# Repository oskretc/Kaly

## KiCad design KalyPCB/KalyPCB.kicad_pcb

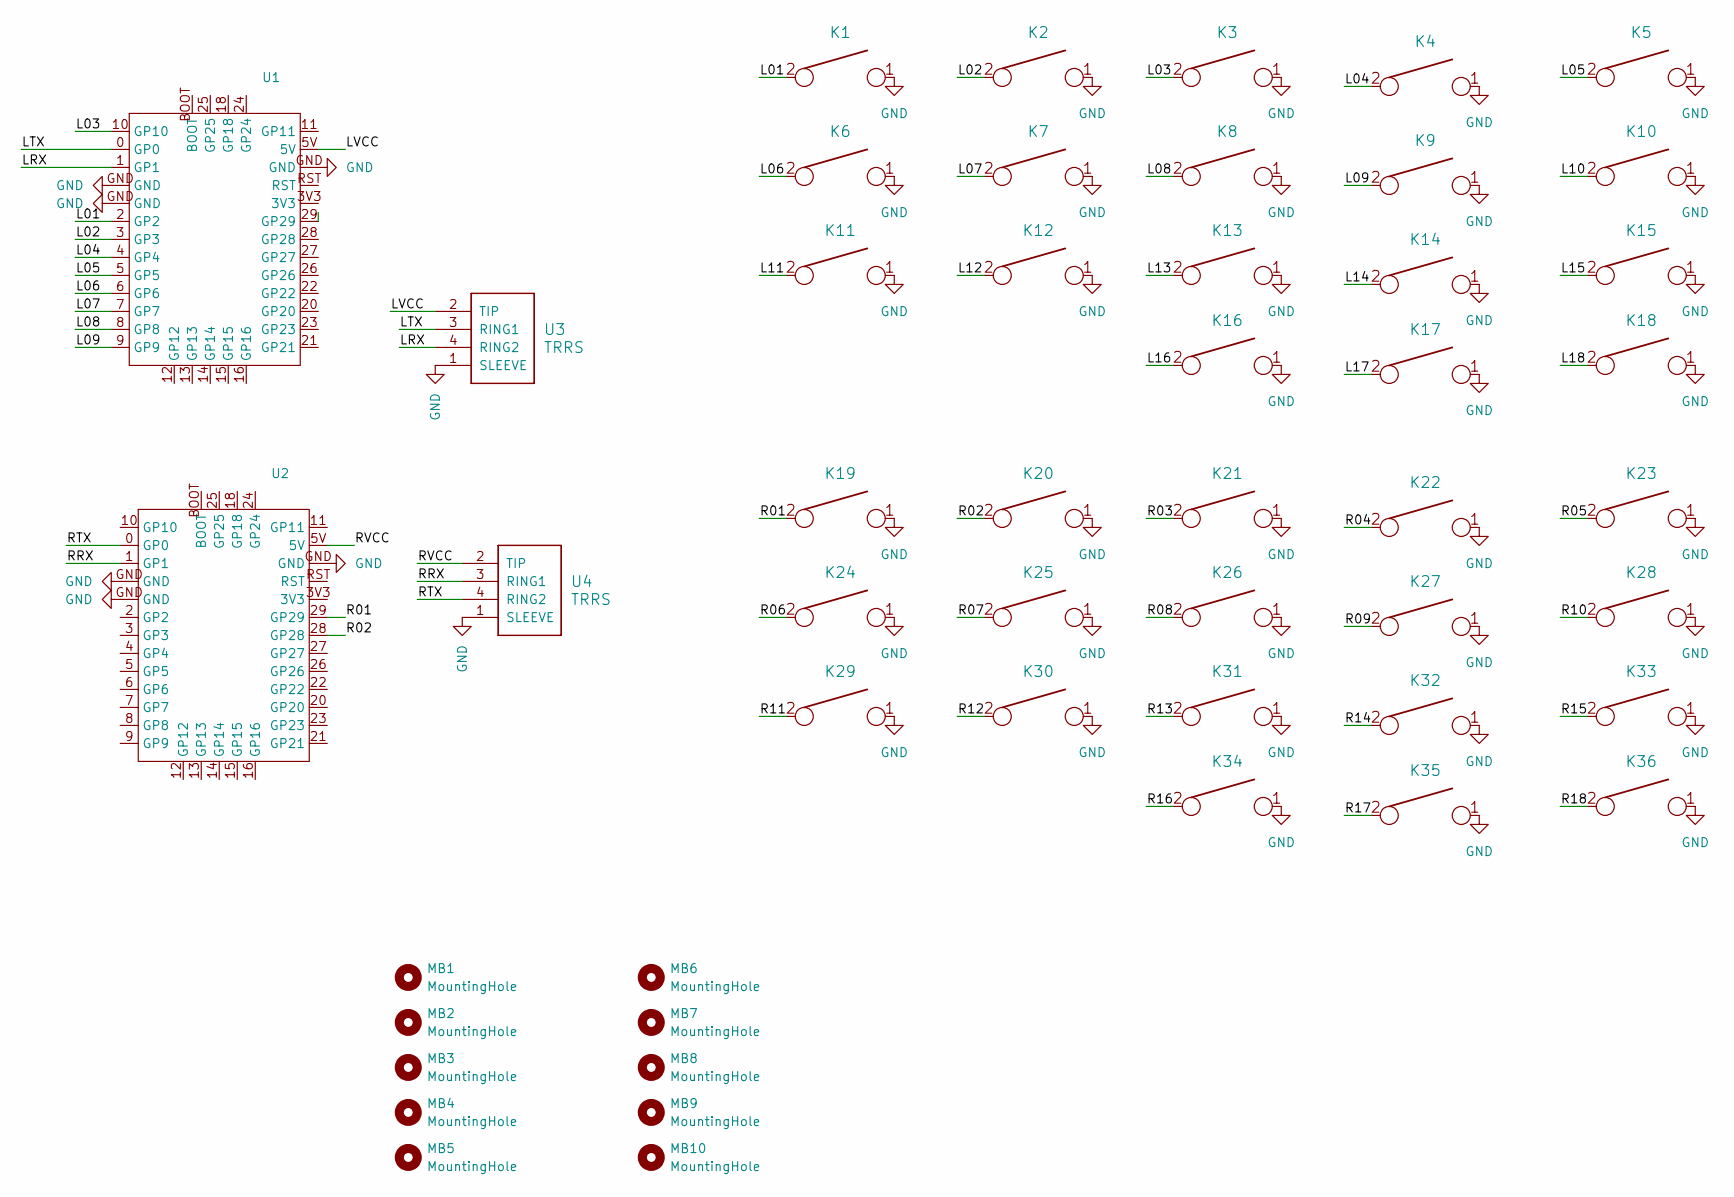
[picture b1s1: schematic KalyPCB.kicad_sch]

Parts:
K1, K2, K3, K4, K5, K6, K7, K8, K9, K10, K11, K12, K13, K14, K15, K16, K17, K18, K19, K20, K21, K22, K23, K24, K25, K26, K27, K28, K29, K30, K31, K32, K33, K34, K35, K36: KEYSW; Kailh_socket_PG1350
MB1, MB2, MB3, MB4, MB5, MB6, MB7, MB8, MB9, MB10: MountingHole; MountingHole_2.2mm_M2-8mm
U1, U2: pro_micro_rp2040
U3, U4: TRRS; TRRS-PJ-320A

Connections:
/L01: K1.2, U1.2 (GP2)
/L02: K2.2, U1.3 (GP3)
/L03: K3.2, U1.10 (GP10)
/L04: K4.2, U1.4 (GP4)
/L05: K5.2, U1.5 (GP5)
/L06: K6.2, U1.6 (GP6)
/L07: K7.2, U1.7 (GP7)
/L08: K8.2, U1.8 (GP8)
/L09: K9.2, U1.9 (GP9)
/L10: K10.2
/L11: K11.2
/L12: K12.2
/L13: K13.2
/L14: K14.2
/L15: K15.2
/L16: K16.2
/L17: K17.2
/L18: K18.2
/LRX: U1.1 (GP1), U3.4 (RING2)
/LTX: U1.0 (GP0), U3.3 (RING1)
/LVCC: U1.5V, U3.2 (TIP)
/R01: K19.2, U2.29 (GP29)
/R02: K20.2, U2.28 (GP28)
/R03: K21.2
/R04: K22.2
/R05: K23.2
/R06: K24.2
/R07: K25.2
/R08: K26.2
/R09: K27.2
/R10: K28.2
/R11: K29.2
/R12: K30.2
/R13: K31.2
/R14: K32.2
/R15: K33.2
/R16: K34.2
/R17: K35.2
/R18: K36.2
/RRX: U2.1 (GP1), U4.3 (RING1)
/RTX: U2.0 (GP0), U4.4 (RING2)
/RVCC: U2.5V, U4.2 (TIP)
GND: K1.1, K2.1, K3.1, K4.1, K5.1, K6.1, K7.1, K8.1, K9.1, K10.1, K11.1, K12.1, K13.1, K14.1, K15.1, K16.1, K17.1, K18.1, K19.1, K20.1, K21.1, K22.1, K23.1, K24.1, K25.1, K26.1, K27.1, K28.1, K29.1, K30.1, K31.1, K32.1, K33.1, K34.1, K35.1, K36.1, U1.GND, U2.GND, U3.1 (SLEEVE), U4.1 (SLEEVE)

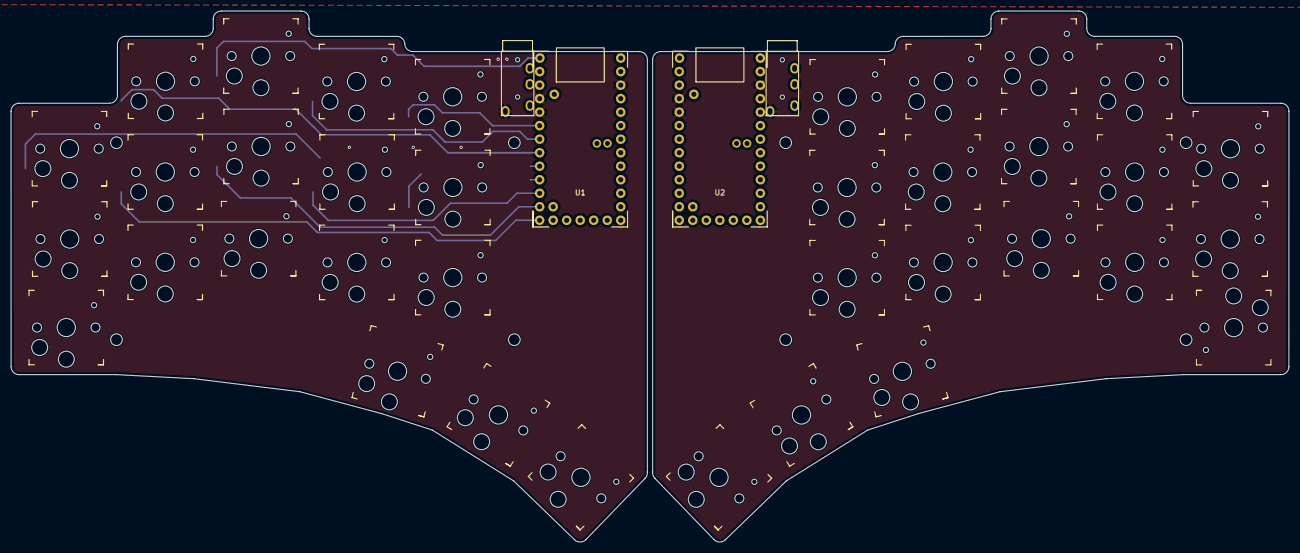
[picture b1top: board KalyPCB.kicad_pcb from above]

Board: 2 copper layers, 240.2 x 99.8 mm, 50 parts (0 on the bottom side), 18 nets.

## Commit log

2026-01-29 deconstruct
2026-01-30 mech ready
2026-01-31 gitteg thert
2026-04-14 added stup
